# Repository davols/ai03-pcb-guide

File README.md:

# ai03-pcb-guide
Woho, my first keeb pcb

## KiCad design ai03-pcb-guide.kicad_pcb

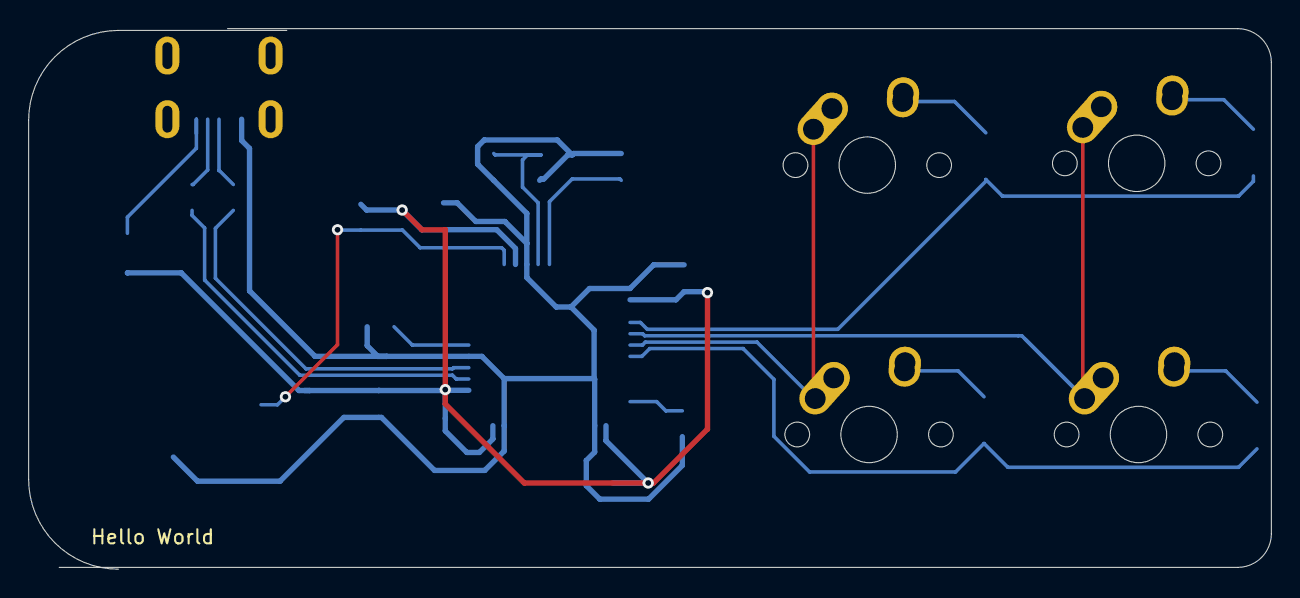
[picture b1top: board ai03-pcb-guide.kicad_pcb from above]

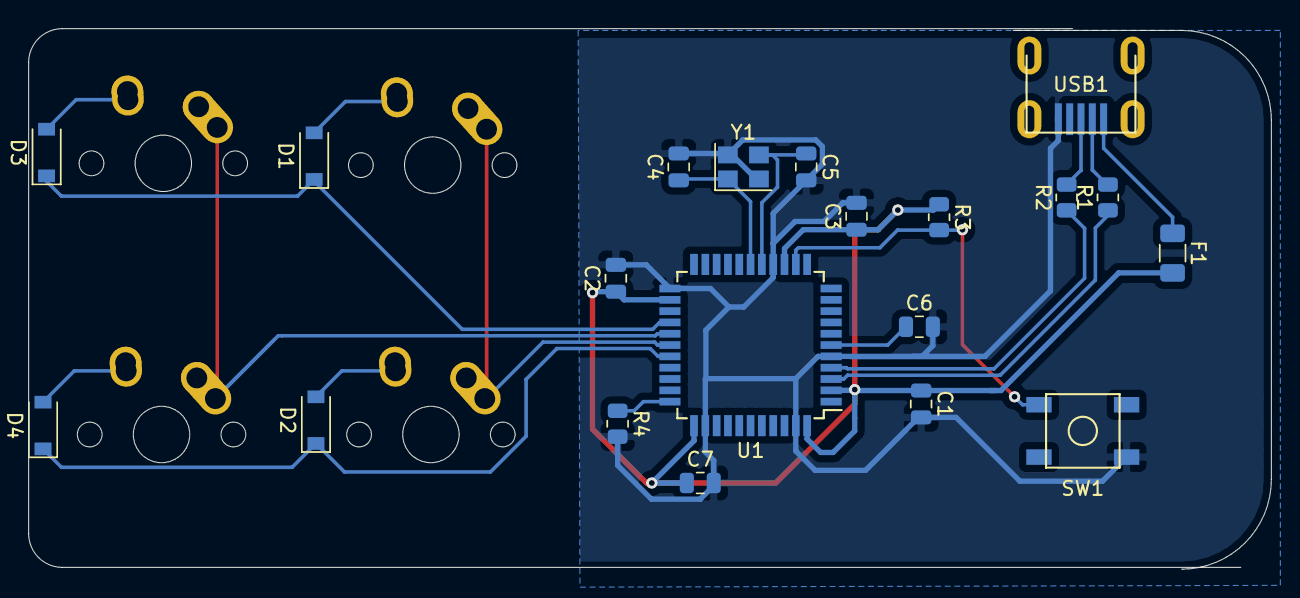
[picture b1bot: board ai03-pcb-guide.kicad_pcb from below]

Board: 2 copper layers, 87.9 x 38.2 mm, 24 parts (20 on the bottom side), 20 nets.

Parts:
C1, C2, C3, C7: 0.1uF; C_0805_2012Metric
C4, C5: 22pF; C_0805_2012Metric
C6: 1uF; C_0805_2012Metric
D1, D2, D3, D4: D_Small; D_SOD-123
F1: 500mA; Fuse_1206_3216Metric
MX1, MX2, MX3, MX4: MX-NoLED; MX-1U-NoLED
R1, R2: 22; R_0805_2012Metric
R3, R4: 10k; R_0805_2012Metric
SW1: SW_Push; SKQG-1155865
U1: ATmega32U4-AU; TQFP-44_10x10mm_P0.8mm
USB1: Molex-0548190589
Y1: 16MHz; Crystal_SMD_3225-4Pin_3.2x2.5mm

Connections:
+5V: C1.1, C2.1, C3.1, C7.1, F1.2, R3.1, U1.2, U1.7, U1.14, U1.24, U1.34, U1.44
COL0: MX1.1, MX2.1, U1.28
COL1: MX3.1, MX4.1, U1.27
D+: R2.2, USB1.3
D-: R1.2, USB1.4
GND: C1.2, C2.2, C3.2, C4.2, C5.2, C6.2, C7.2, R4.2, SW1.1, U1.5, U1.15, U1.23, U1.35, U1.43, USB1.1, Y1.2, Y1.4
unnamed: C4.1, U1.17, Y1.1
unnamed: C5.1, U1.16, Y1.3
unnamed: C6.1, U1.6
unnamed: D1.2, MX1.2
unnamed: D2.2, MX2.2
unnamed: D3.2, MX3.2
unnamed: D4.2, MX4.2
unnamed: R1.1, U1.3
unnamed: R2.1, U1.4
unnamed: R3.2, SW1.2, U1.13
unnamed: R4.1, U1.33
ROW0: D1.1, D3.1, U1.26
ROW1: D2.1, D4.1, U1.29
VCC: F1.1, USB1.5

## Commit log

2021-10-24 Add submodules
2021-10-24 add libs
2021-10-24 Woop woop. schematic done?
2021-10-24 WOooop
2021-10-24 Prettify pcb
